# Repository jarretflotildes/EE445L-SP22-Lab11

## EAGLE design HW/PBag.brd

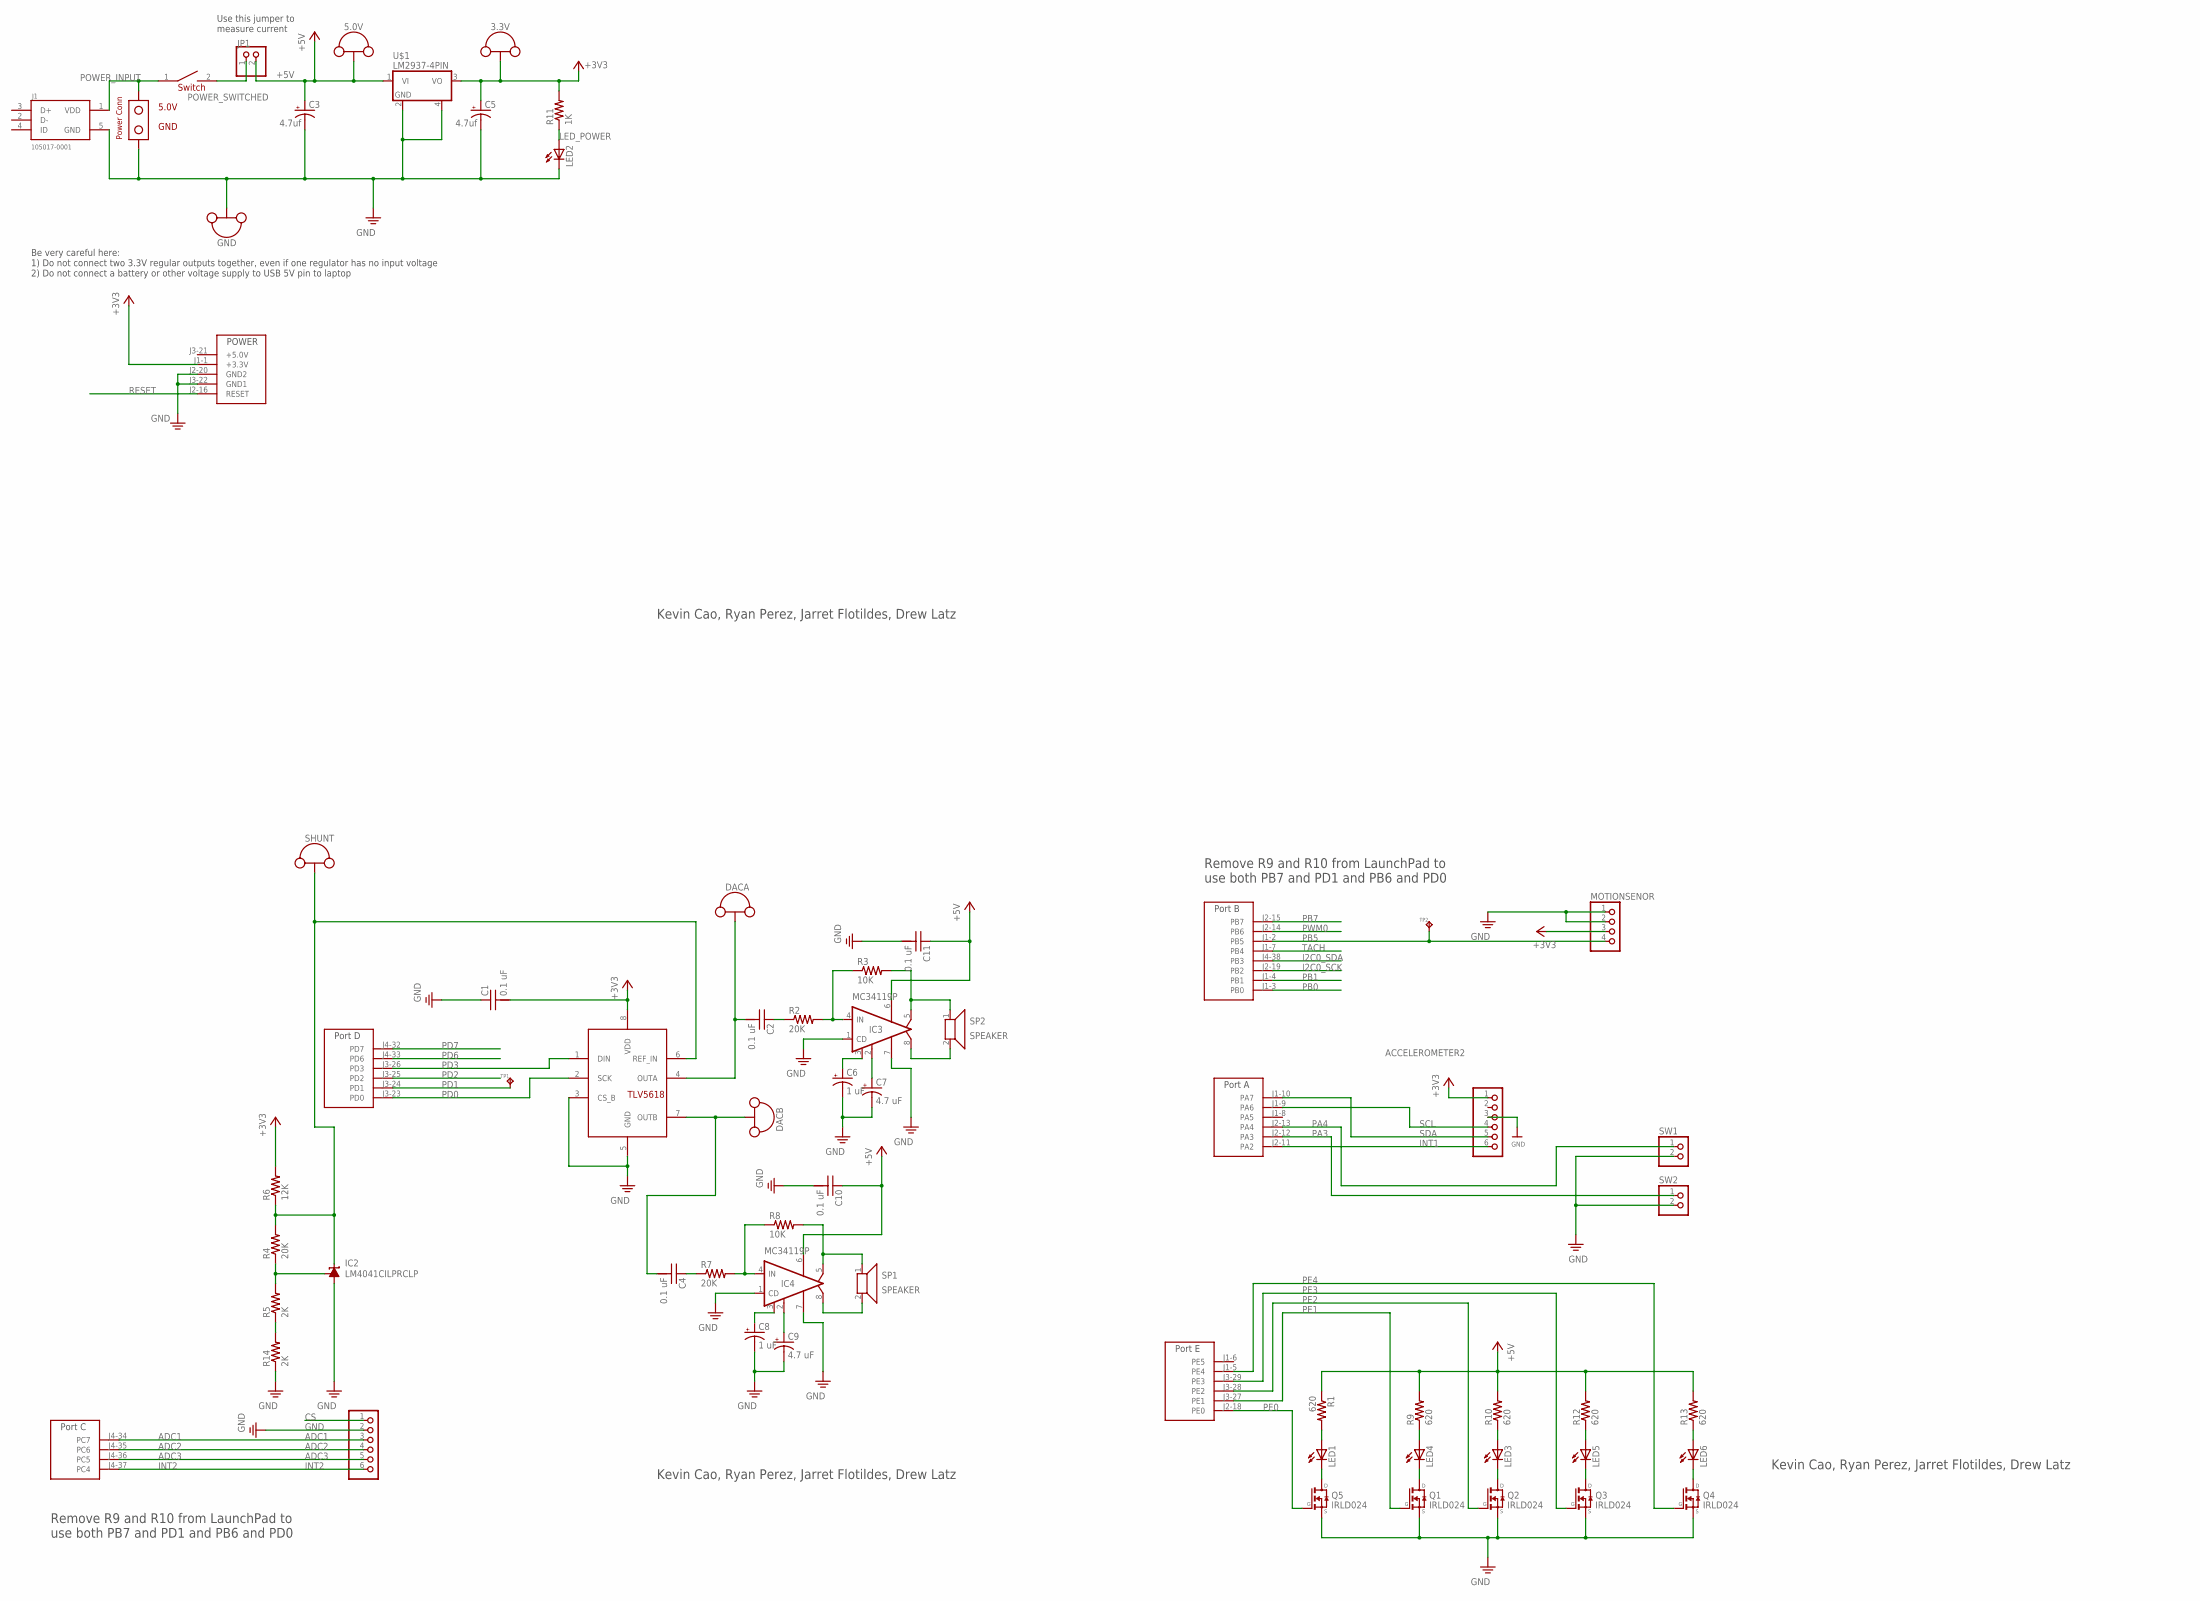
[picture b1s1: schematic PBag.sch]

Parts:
3.3V, 5.0V: TP_LOOP
ACCELEROMETER1, ACCELEROMETER2: HEADER-1X670MIL; 1X06_ROUND_70
C1, C2, C4, C10, C11: 0.1 uF; CAP100MIL
C3, C5: 4.7uf; CAP200MILPOLARIZED
C6, C8: 1 uF; CAP200MILPOLARIZED
C7, C9: 4.7 uF; CAP200MILPOLARIZED
DAC: TLV5618; DIL08
DACA: TP_LOOP
DACB: TP_LOOP
GND: TP_LOOP
IC2: LM4041CILPRCLP; LP_O-PBCY-W3
IC3, IC4: MC34119P; DIL08
J1: 105017-0001; MOLEX_105017-0001
JP1: PINHD-1X2; 1X02
LED1, LED3, LED4, LED5, LED6: LED5MM
LED2: LED3MM
MOTIONSENOR: PINHD-1X4/90; 1X04/90
Q1, Q2, Q3, Q4, Q5: IRLD024
R1, R9, R10, R12, R13: 620; RES200MIL
R2, R4, R7: 20K; RES200MIL
R3, R8: 10K; RES200MIL
R5, R14: 2K; RES200MIL
R6: 12K; RES200MIL
R11: 1K; RES200MIL
SHUNT: TP_LOOP
SP1, SP2: SPEAKER; 1X02
SW1, SW2: PINHD-1X2; 1X02
TP1, TP2: TP_KEYSTONE500X; P1.1MM
U$1: LM2937-4PIN; TO220-4PIN
U$2: TM4C_BP; TM4C_BOOSTER_PACK
U$5: POWER_CONN
U$6: SW_POWER_100MIL; SW_POWER

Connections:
+3V3: 3.3V.P$1, 3.3V.P$2, ACCELEROMETER2.1, C1.2, C5.+, DAC.8 (VDD), MOTIONSENOR.3, R6.2, R11.2, U$1.3 (VO), U$2.J1-1 (+3.3V)
+5V: 5.0V.P$1, 5.0V.P$2, C3.+, C10.1, C11.1, IC3.6 (VCC), IC4.6 (VCC), JP1.2, R1.1, R9.2, R10.2, R12.2, R13.2, U$1.1 (VI)
ADC1: ACCELEROMETER1.3, U$2.J4-34 (PC7)
ADC2: ACCELEROMETER1.4, U$2.J4-35 (PC6)
ADC3: ACCELEROMETER1.5, U$2.J4-36 (PC5)
CS: ACCELEROMETER1.1
GND: ACCELEROMETER1.2, ACCELEROMETER2.3, C1.1, C3.-, C5.-, C6.-, C7.-, C8.-, C9.-, C10.2, C11.2, DAC.3 (CS_B), DAC.5 (GND), GND.P$1, GND.P$2, IC2.3 (A), IC3.1 (CD), IC3.7 (GND), IC4.1 (CD), IC4.7 (GND), J1.5 (GND), LED2.K (C), MOTIONSENOR.1, MOTIONSENOR.2, Q1.P$4 (S), Q2.P$4 (S), Q3.P$4 (S), Q4.P$4 (S), Q5.P$4 (S), R14.1, SW1.2, SW2.2, U$1.2 (GND), U$1.4 (PAD), U$2.J2-20 (GND2), U$2.J3-22 (GND1), U$5.GND
I2C0_SCK: U$2.J2-19 (PB2)
I2C0_SDA: U$2.J4-38 (PB3)
INT1: ACCELEROMETER2.6, U$2.J2-11 (PA2)
INT2: ACCELEROMETER1.6, U$2.J4-37 (PC4)
LED1: LED1.A, R1.2
LED1D: LED1.K (C), Q5.P$1 (D)
LED3: LED3.A, R10.1
LED3D: LED3.K (C), Q2.P$1 (D)
LED4: LED4.A, R9.1
LED4D: LED4.K (C), Q1.P$1 (D)
LED5: LED5.A, R12.1
LED5D: LED5.K (C), Q3.P$1 (D)
LED6: LED6.A, R13.1
LED6D: LED6.K (C), Q4.P$1 (D)
LED_POWER: LED2.A, R11.1
MC1C6: C6.+, IC3.3 (FC1)
MC1C7: C7.+, IC3.2 (FC2)
MC1IN: IC3.4 (IN), R2.2, R3.1
MC2C8: C8.+, IC4.3 (FC1)
MC2C9: C9.+, IC4.2 (FC2)
MC2IN: IC4.4 (IN), R7.2, R8.1
OUTA: C2.2, DAC.4 (OUTA), DACA.P$1, DACA.P$2
OUTACON: C2.1, R2.1
OUTB: C4.2, DAC.7 (OUTB), DACB.P$1, DACB.P$2
OUTBCON: C4.1, R7.1
PA3: SW2.1, U$2.J2-12 (PA3)
PA4: SW1.1, U$2.J2-13 (PA4)
PB0: U$2.J1-3 (PB0)
PB1: U$2.J1-4 (PB1)
PB5: MOTIONSENOR.4, TP2.TP, U$2.J1-2 (PB5)
PB7: U$2.J2-15 (PB7)
PD0: DAC.2 (SCK), U$2.J3-23 (PD0)
PD1: TP1.TP, U$2.J3-24 (PD1)
PD2: U$2.J3-25 (PD2)
PD3: DAC.1 (DIN), U$2.J3-26 (PD3)
PD6: U$2.J4-33 (PD6)
PD7: U$2.J4-32 (PD7)
PE0: Q5.P$3 (G), U$2.J2-18 (PE0)
PE1: Q1.P$3 (G), U$2.J3-27 (PE1)
PE2: Q2.P$3 (G), U$2.J3-28 (PE2)
PE3: Q3.P$3 (G), U$2.J3-29 (PE3)
PE4: Q4.P$3 (G), U$2.J1-5 (PE4)
POWER_INPUT: J1.1 (VDD), U$5.VDD, U$6.1
POWER_SWITCHED: JP1.1, U$6.2
PWM0: U$2.J2-14 (PB6)
R5-14: R5.1, R14.2
RESET: U$2.J2-16 (RESET)
SCL: ACCELEROMETER2.4, U$2.J1-9 (PA6)
SDA: ACCELEROMETER2.5, U$2.J1-10 (PA7)
SHUNT: IC2.1 (FB), R4.1, R5.2
SHUNTREFIN: DAC.6 (REF_IN), IC2.2 (C), R4.2, R6.1, SHUNT.P$1, SHUNT.P$2
SP15: IC4.5 (VO1), R8.2, SP1.1
SP18: IC4.8 (VO2), SP1.2
SP25: IC3.5 (VO1), R3.2, SP2.1
SP28: IC3.8 (VO2), SP2.2
TACH: U$2.J1-7 (PB4)

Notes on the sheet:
Remove R9 and R10 from LaunchPad to use both PB7 and PD1 and PB6 and PD0
Kevin Cao, Ryan Perez, Jarret Flotildes, Drew Latz
Be very careful here: 1) Do not connect two 3.3V regular outputs together, even if one regulator has no input voltage 2) Do not connect a battery or other voltage supply to USB 5V pin to laptop
Use this jumper to measure current

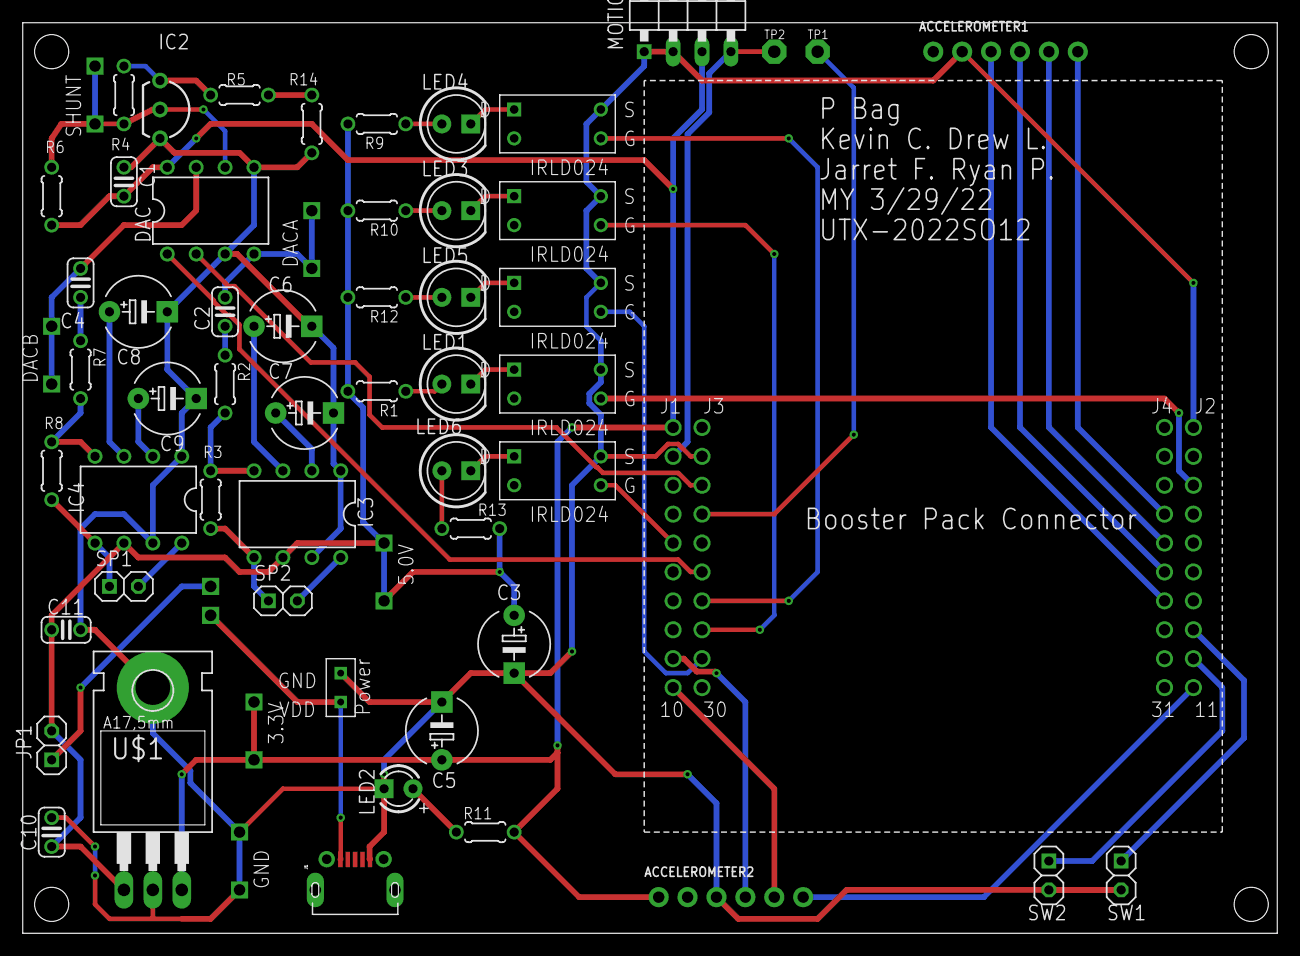
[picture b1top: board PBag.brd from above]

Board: 2 copper layers, 110.2 x 80.0 mm, 61 parts (0 on the bottom side), 51 nets.

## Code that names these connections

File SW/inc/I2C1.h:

/**
 * @file      I2C1.h
 * @brief     Low-level software driver for I2C
 * @details   TM4C123 is master. I2C1 is connected to PD0=SCL, PD1=SDA<br>
 * This file originally comes from the TIDA-010021 Firmware (tidcf48.zip) and<br>
 * was modified by Pololu to support the MSP432P401R.  Modified again for TM4C123
 * @version   SSD1306 EE319K
 * @author    Daniel Valvano and Jonathan Valvano
 * @copyright Copyright 2021 by Jonathan W. Valvano, valvano@mail.utexas.edu,
 * @warning   AS-IS
 * @note      For more information see  http://users.ece.utexas.edu/~valvano/
 * @date      Jan 2, 2021
<table>
<caption id="I2C1ports">I2C connected to I2C1</caption>
<tr><th>Pin   <th>signal
<tr><td>GND   <td>ground
<tr><td>VIN   <td>3.3V
<tr><td>PA7   <td>I2C SDA data (bidirectional)
<tr><td>PA6   <td>I2C SCL clock (TM4C123 output)
</table>
 ******************************************************************************/


/* This example accompanies the books
   "Embedded Systems: Introduction to ARM Cortex M Microcontrollers",
      ISBN: 978-1469998749, Jonathan Valvano, copyright (c) 2020
   "Embedded Systems: Real Time Interfacing to ARM Cortex M Microcontrollers",
      ISBN: 978-1463590154, Jonathan Valvano, copyright (c) 2020
   "Embedded Systems: Real-Time Operating Systems for ARM Cortex-M Microcontrollers",
      ISBN: 978-1466468863, Jonathan Valvano, copyright (c) 2020

 Copyright 2021 by Jonathan W. Valvano, valvano@mail.utexas.edu
    You may use, edit, run or distribute this file
    as long as the above copyright notice remains
 THIS SOFTWARE IS PROVIDED "AS IS".  NO WARRANTIES, WHETHER EXPRESS, IMPLIED
 OR STATUTORY, INCLUDING, BUT NOT LIMITED TO, IMPLIED WARRANTIES OF
 MERCHANTABILITY AND FITNESS FOR A PARTICULAR PURPOSE APPLY TO THIS SOFTWARE.
 VALVANO SHALL NOT, IN ANY CIRCUMSTANCES, BE LIABLE FOR SPECIAL, INCIDENTAL,
 OR CONSEQUENTIAL DAMAGES, FOR ANY REASON WHATSOEVER.
 For more information about my classes, my research, and my books, see
 http://users.ece.utexas.edu/~valvano/
 */

// TM4C123 hardware
// SDA    PA7 I2C data
// SCL    PA6 I2C clock
/*
 *  I2C0 Conncection | I2C1 Conncection | I2C2 Conncection | I2C3 Conncection
 *  ---------------- | ---------------- | ---------------- | ----------------
 *  SCL -------- PB2 | SCL -------- PA6 | SCL -------- PE4 | SCL -------- PD0
 *  SDA -------- PB3 | SDA -------- PA7 | SDA -------- PE5 | SDA -------- PD1
 */
 #ifndef _I2C1_H_
#define _I2C1_H_
#include <stdint.h>

/**
 * I2C1_Init
 * ----------
 * let t be bus period, let F be bus frequency,
 * let f be I2C frequency.
 * at F=80 MHz, I2C period = (TPR+1)*250ns.<br> 
 * f=400kHz,    I2C period = 20*(TPR+1)*12.5ns = 2.5us, with TPR=9<br>
 * I2C period, 1/f = 20*(TPR+1)*t <br>
 * F/f = 20*(TPR+1)<br>
 * TPR = (F/f/20)-1 
 * @param  I2Cfreq  desired frequency of I2C in Hz.
 * @param  busFreq  bus frequency in Hz.
 * ----------
 * @brief write 1 or more bytes to I2C1.
 */
void I2C1_Init(uint32_t I2Cfreq, uint32_t busFreq);

/**
 * I2C1_Send
 * ----------
 * @param  slaveAddr  address of slave device.
 * @param  pData      data address of data to be writen.
 * @param  count      number of bytes to be writen.
 * ----------
 * @brief write 1 or more bytes to I2C1.
 */
int I2C1_Send(uint8_t slaveAddr, uint8_t *pData, uint32_t count);

/**
 * I2C1_Send1
 * ----------
 * @param  slaveAddr  address of slave device.
 * @param  data       data to be writen.
 * ----------
 * @brief write 1 byte to I2C1.
 */
 int I2C1_Send1(uint8_t slaveAddr, uint8_t data);
 
 /**
 * I2C1_Send2
 * ----------
 * @param  slaveAddr  address of slave device.
 * @param  data1      first data to be writen.
 * @param  data2      second data to be writen.
 * ----------
 * @brief write 1 byte to I2C1.
 */
 int I2C1_Send2(int8_t slave, uint8_t data1, uint8_t data2);
 
 /**
 * I2C1_Send3
 * ----------
 * @param  slaveAddr  address of slave device.
 * @param  data1      data to be writen.
 * @param  data2      data to be writen.
 * @param  data3      data to be writen.
 * ----------
 * @brief write 3 bytes to I2C1.
 */
 int I2C1_Send3(uint8_t slaveAddr, uint8_t data1, uint8_t data2, uint8_t data3);
 
/**
 * I2C1_Send4
 * ----------
 * @param  slaveAddr  address of slave device.
 * @param  data1      data to be writen.
 * @param  data2      data to be writen.
 * @param  data3      data to be writen.
 * @param  data4      data to be writen.
 * ----------
 * @brief write 4 bytes to I2C1.
 */
 int I2C1_Send4(uint8_t slaveAddr, uint8_t data1, uint8_t data2, uint8_t data3, uint8_t data4);

/**
 * I2C1_Recv
 * ----------
 * @param  slaveAddr  address of slave device.
 * @param  pData      data address to store read data.
 * @param  count      number of bytes to be read.
 * ----------
 * @brief read 1 or more bytes from I2C1.
 */
int I2C1_Recv(uint8_t slaveAddr, uint8_t *pData, uint32_t count);

/**
 * I2C1_Recv3
 * ----------
 * @param  slaveAddr  address of slave device.
 * @param  data       data address to store read data.
 * @param  count      number of bytes to be read.
 * @brief read 2 or more bytes from I2C1.
 */
int I2C1_Recv3(uint8_t slaveAddr, uint8_t data[3]);

int I2C1_RecvTest(uint8_t slaveAddr, uint8_t subAddress ,uint8_t *data);

/**
 * I2C1_Recv6
 * ----------
 * @param  slaveAddr  address of slave device.
 * @param  data       data address to store read data.
 * @param  count      number of bytes to be read.
 * @brief read 6 bytes from I2C1.
 */
int I2C1_Recv6(uint8_t slaveAddr, uint8_t subAddress, uint8_t data[6]);

/**
 * I2C1_SendData
 * ----------
 * @param  slaveAddr  address of slave device.
 * @param  pData      data address of data to be writen.
 * @param  count      number of bytes to be writen.
 * ----------
 * @brief write many bytes to I2C1.
 */
int I2C1_SendData(uint8_t slaveAddr, uint8_t *pData, uint32_t count);


#endif //_I2C1_H_

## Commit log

2022-04-25 removed lab 10 stuff, edited motion
2022-05-02 added motion
2022-05-02 led fixed

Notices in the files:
parts and their libraries:
microbuilder: This work is placed in the public domain, and may be freely used for commercial and non-commercial work with the following conditions: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
